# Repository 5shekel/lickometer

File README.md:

# lickometer
a simple transistor switch turned on by touch  

more here https://groups.google.com/forum/#!msg/hasadna/RWvjrGsnScA/P2cK_W5ywc8J

we used this circuit to cut cardboard boards for workshops
http://telavivmakers.org/Cutting_machine

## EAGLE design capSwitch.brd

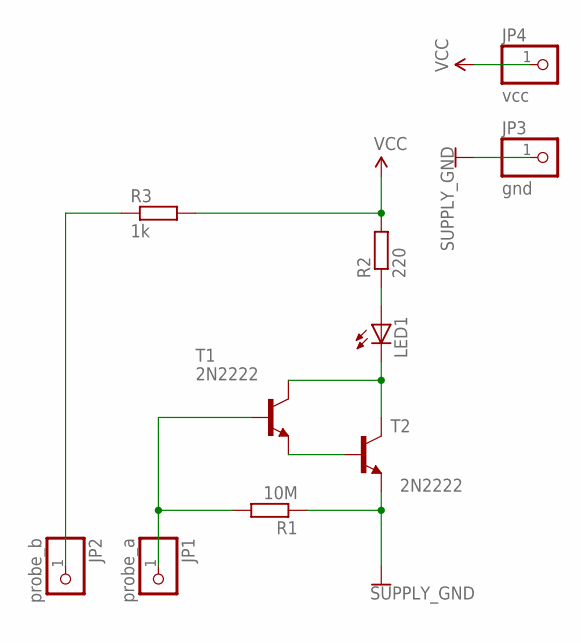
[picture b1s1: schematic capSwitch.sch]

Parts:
JP1: probe_a; 1X01_OVAL
JP2: probe_b; 1X01_OVAL
JP3: gnd; 1X01_OVAL
JP4: vcc; 1X01_OVAL
LED1: LED5MM
R1: 10M; RTH025W
R2: 220; RTH025W
R3: 1k; RTH025W
T1, T2: 2N2222; TO92-EBC-OVAL

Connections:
GND: JP3.1, R1.1, T2.E
unnamed: LED1.A, R2.1
unnamed: LED1.K (C), T1.C, T2.C
unnamed: JP2.1, R3.1
unnamed: JP1.1, R1.2, T1.B
unnamed: T1.E, T2.B
VCC: JP4.1, R2.2, R3.2

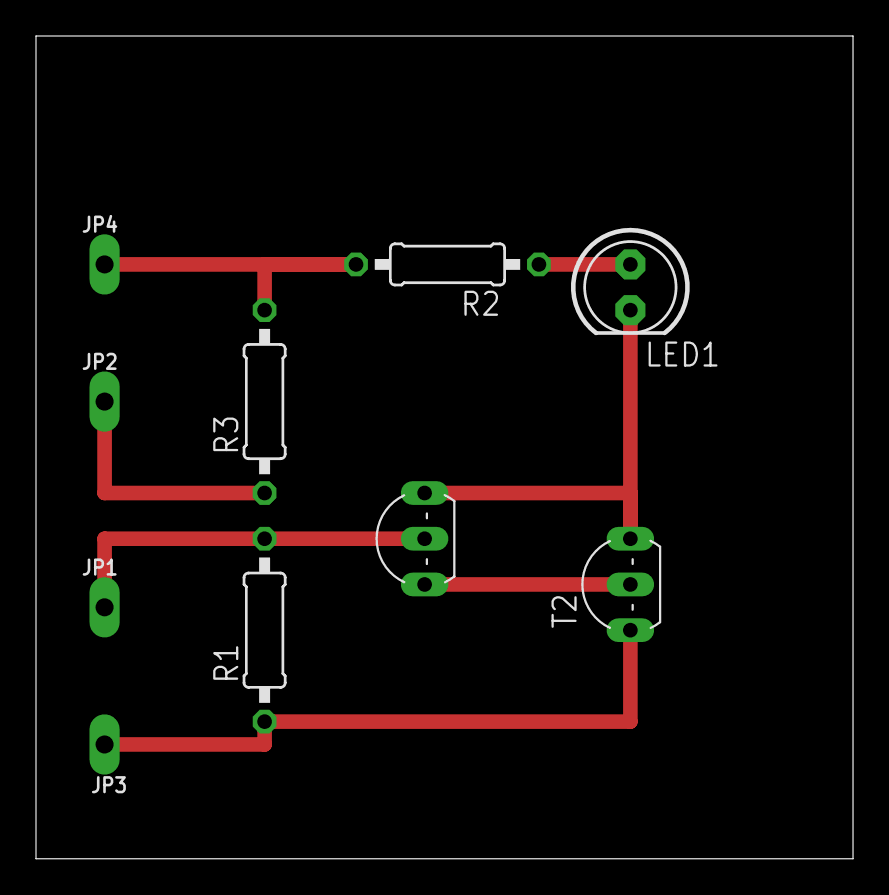
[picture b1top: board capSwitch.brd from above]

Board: 2 copper layers, 45.4 x 45.7 mm, 10 parts (0 on the bottom side), 7 nets.

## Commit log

2014-11-13 :boom::camel: Added .gitattributes & .gitignore files
2014-11-13 first rev
    DIP pack, no traces
2014-11-13 darlington edition
2014-11-13 changed cap to 10M
2014-11-13 refined board, ready to be etched
2015-02-25 removed non eagle ignores
2017-04-17 added workshops

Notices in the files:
parts and their libraries:
microbuilder: This work is placed in the public domain, and may be freely used for commercial and non-commercial work with the following conditions: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
SparkFun-Aesthetics: Licensing: CC v3.0 Share-Alike You are welcome to use this library for commercial purposes.
